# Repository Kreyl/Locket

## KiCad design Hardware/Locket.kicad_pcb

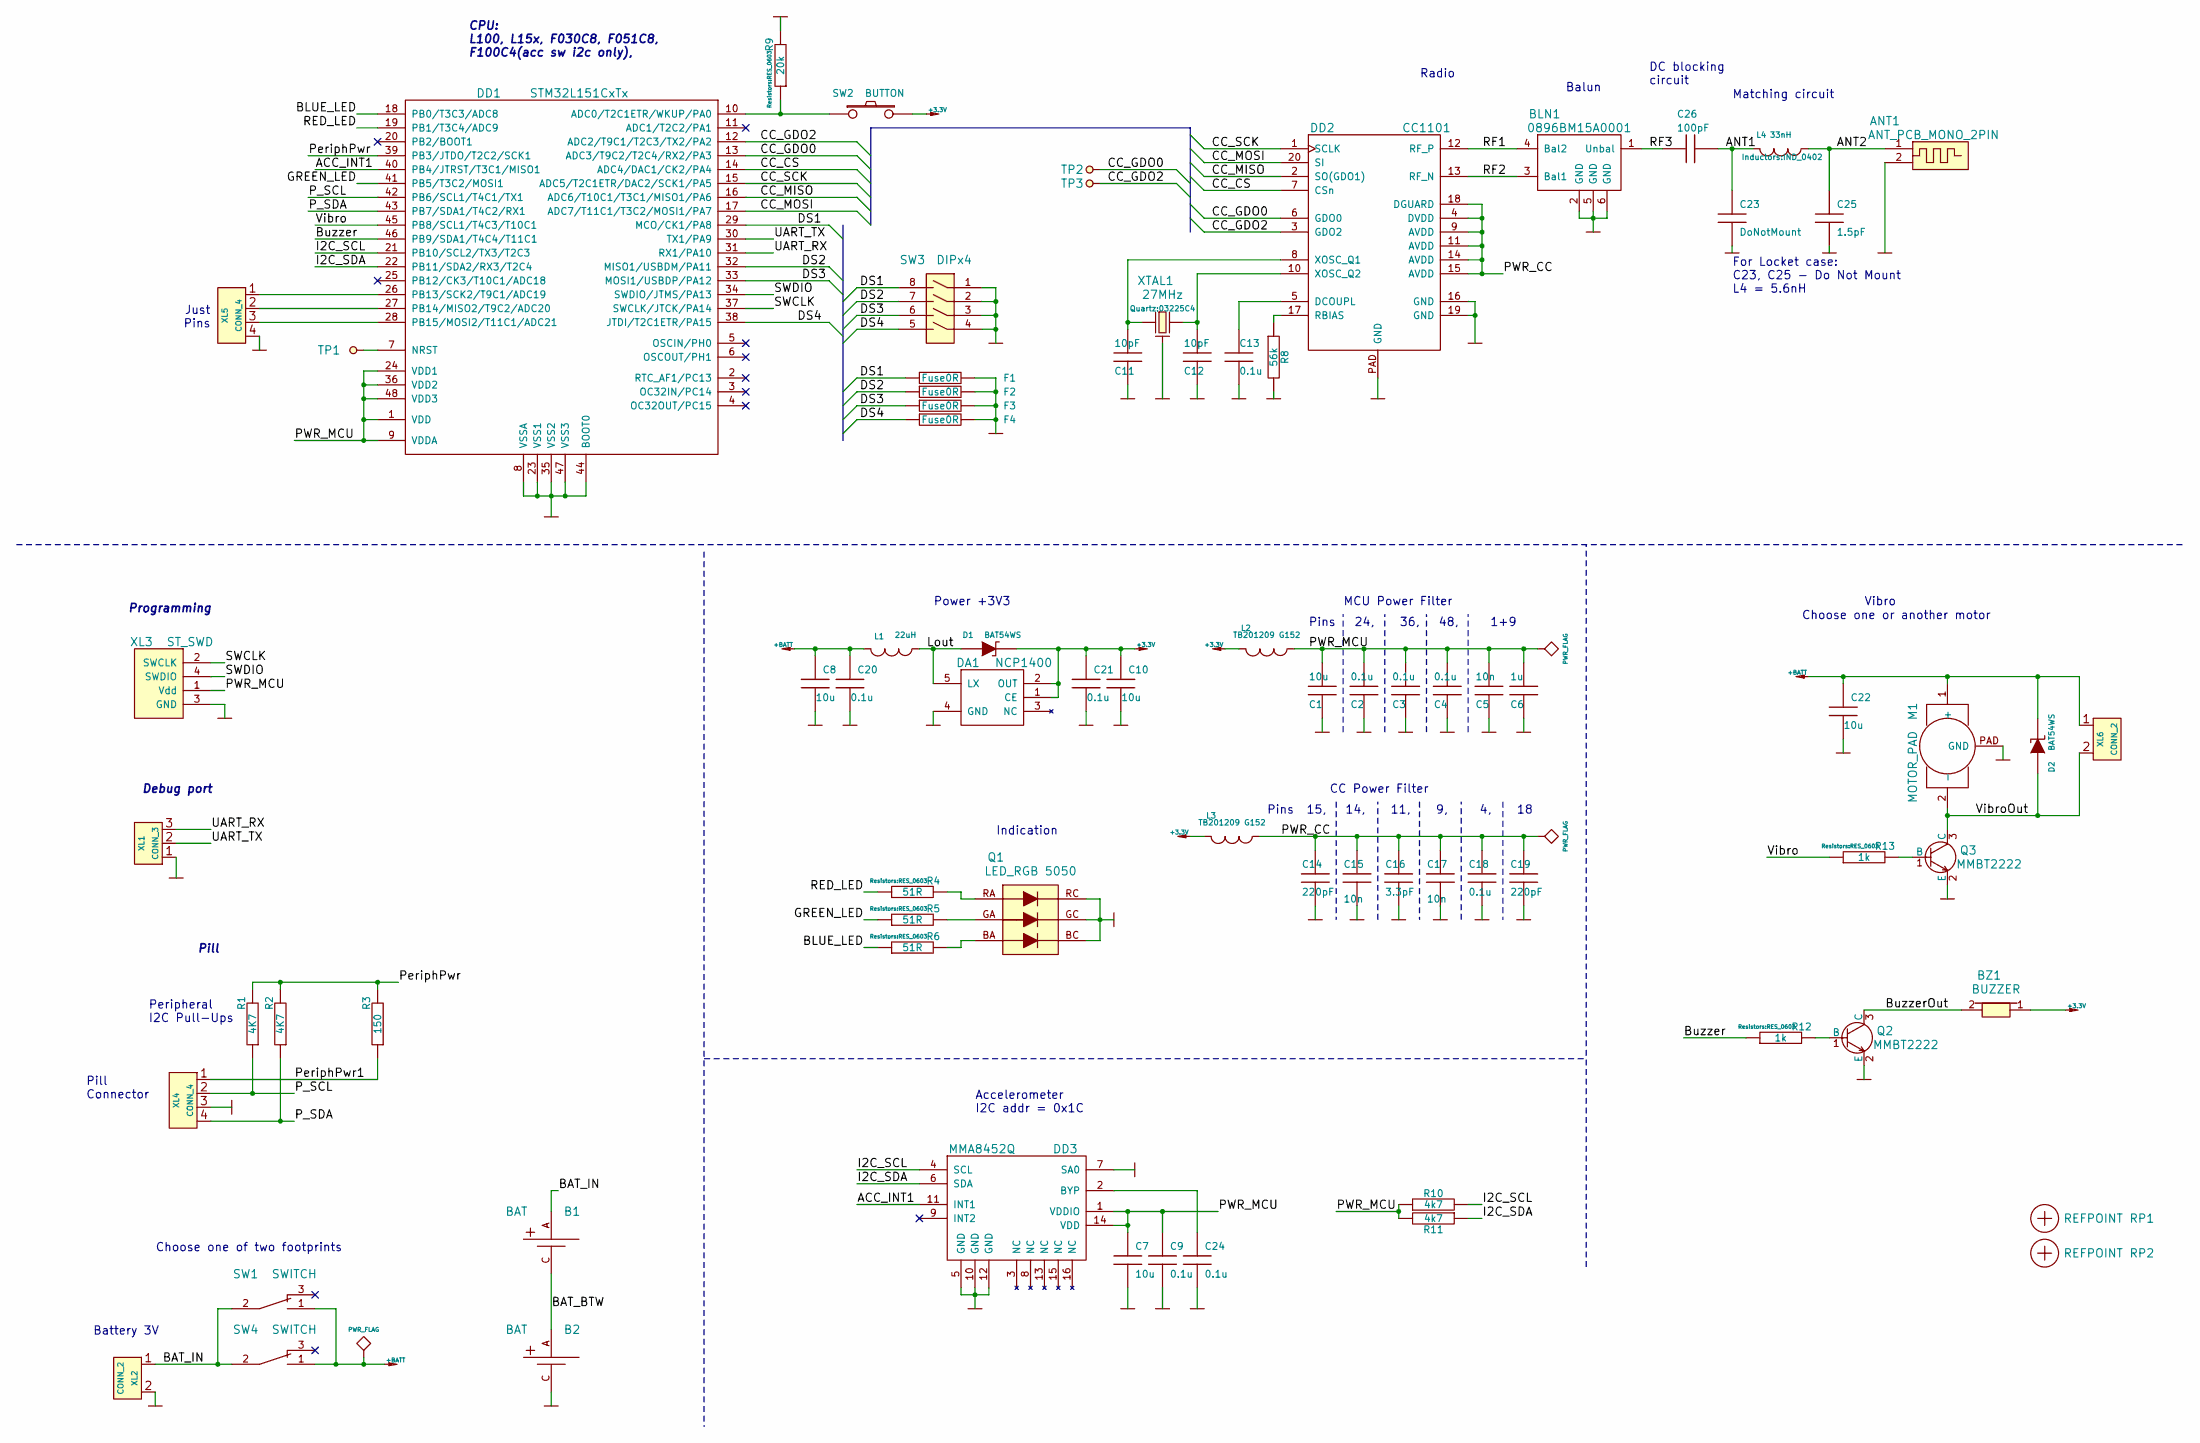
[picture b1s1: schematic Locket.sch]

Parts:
ANT1: ANT_PCB_MONO_2PIN; ANT_868_ROUND_F
B1, B2: BAT; BATTERY_AAA_X1
BLN1: 0896BM15A0001; BALUN_JOHANSON868
BZ1: BUZZER; BUZZER_HC0903
C1, C7, C8, C10, C22: 10u; CAP_0805
C2, C3, C4, C9, C13, C18, C20, C21, C24: 0.1u; CAP_0603
C5, C15, C17: 10n; CAP_0603
C6: 1u; CAP_0603
C11, C12: 10pF; CAP_0603
C14, C19: 220pF; CAP_0603
C16: 3.3pF; CAP_0603
C23: DoNotMount; CAP_0402
C25: 1.5pF; CAP_0402
C26: 100pF; CAP_0402
D1, D2: BAT54WS; SOD323
DA1: NCP1400; SOT23-5
DD1: STM32L151CxTx; LQFP48
DD2: CC1101; QFN20
DD3: MMA8452Q; QFN16_5_3
F1, F2, F3, F4: Fuse0R; RES_0603_FUSE
L1: 22uH; IND_1210_LQH32C
L2, L3: TB201209 G152; IND_0805
L4: 33nH; IND_0402
M1: MOTOR_PAD; MOTOR_KHN4NX
Q1: LED_RGB 5050; 5050
Q2, Q3: MMBT2222; SOT23-3
R1, R2: 4K7; RES_0603
R3: 150; RES_0603
R4, R5, R6: 51R; RES_0603
R8: 56k; RES_0603
R9: 20k; RES_0603
R10, R11: 4k7; RES_0603
R12, R13: 1k; RES_0603
RP1, RP2: REFPOINT; REF_POINT_1MM
SW1: SWITCH; SW_SS-6
SW2: BUTTON; BTN_6x6
SW3: DIPx4; DIP_SMD_X4
SW4: SWITCH; SW_SS-1P2T
TP1, TP2, TP3: TESTPOINT; TESTPOINT_1MM
XL1: CONN_3; PLS-3
XL2, XL6: CONN_2; PLS-2
XL3: ST_SWD; PLS-4
XL4, XL5: CONN_4; PLS-4
XTAL1: 27MHz; 03225C4

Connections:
+3.3V: BZ1.1, C10.1, C21.1, D1.C, DA1.1 (CE), DA1.2 (OUT), L2.2, L3.2, SW2.2
+BATT: C8.1, C20.1, C22.1, D2.C, L1.2, M1.1 (+), SW1.1, SW4.1, XL6.1
/ACC_INT1: DD1.40 (PB4/JTRST/T3C1/MISO1), DD3.11 (INT1)
/ANT1: C23.1, C26.1, L4.2
/ANT2: ANT1.1, C25.1, L4.1
/BAT_BTW: B1.C, B2.A
/BAT_IN: B1.A, SW1.2, SW4.2, XL2.1
/BLUE_LED: DD1.18 (PB0/T3C3/ADC8), R6.1
/Buzzer: DD1.46 (PB9/SDA1/T4C4/T11C1), R12.1
/BuzzerOut: BZ1.2, Q2.3 (C)
/CC_CS: DD1.14 (ADC4/DAC1/CK2/PA4), DD2.7 (CSn)
/CC_GDO0: DD1.13 (ADC3/T9C2/T2C4/RX2/PA3), DD2.6 (GDO0), TP2.1
/CC_GDO2: DD1.12 (ADC2/T9C1/T2C3/TX2/PA2), DD2.3 (GDO2), TP3.1
/CC_MISO: DD1.16 (ADC6/T10C1/T3C1/MISO1/PA6), DD2.2 (SO(GDO1))
/CC_MOSI: DD1.17 (ADC7/T11C1/T3C2/MOSI1/PA7), DD2.20 (SI)
/CC_SCK: DD1.15 (ADC5/T2C1ETR/DAC2/SCK1/PA5), DD2.1 (SCLK)
/DS1: DD1.29 (MCO/CK1/PA8), F1.1, SW3.8
/DS2: DD1.32 (MISO1/USBDM/PA11), F2.1, SW3.7
/DS3: DD1.33 (MOSI1/USBDP/PA12), F3.1, SW3.6
/DS4: DD1.38 (JTDI/T2C1ETR/PA15), F4.1, SW3.5
/GREEN_LED: DD1.41 (PB5/T3C2/MOSI1), R5.1
/I2C_SCL: DD1.21 (PB10/SCL2/TX3/T2C3), DD3.4 (SCL), R10.2
/I2C_SDA: DD1.22 (PB11/SDA2/RX3/T2C4), DD3.6 (SDA), R11.1
/Lout: D1.A, DA1.5 (LX), L1.1
/PWR_CC: C14.1, C15.1, C16.1, C17.1, C18.1, C19.1, DD2.4 (DVDD), DD2.9 (AVDD), DD2.11 (AVDD), DD2.14 (AVDD), DD2.15 (AVDD), DD2.18 (DGUARD), L3.1
/PWR_MCU: C1.1, C2.1, C3.1, C4.1, C5.1, C6.1, C7.1, C9.1, DD1.1 (VDD), DD1.9 (VDDA), DD1.24 (VDD1), DD1.36 (VDD2), DD1.48 (VDD3), DD3.1 (VDDIO), DD3.14 (VDD), L2.1, R10.1, R11.2, XL3.1 (Vdd)
/P_SCL: DD1.42 (PB6/SCL1/T4C1/TX1), R1.1, XL4.2 (PM)
/P_SDA: DD1.43 (PB7/SDA1/T4C2/RX1), R2.1, XL4.4
/PeriphPwr: DD1.39 (PB3/JTDO/T2C2/SCK1), R1.2, R2.2, R3.2
/PeriphPwr1: R3.1, XL4.1
/RED_LED: DD1.19 (PB1/T3C4/ADC9), R4.1
/RF1: BLN1.4 (Bal2), DD2.12 (RF_P)
/RF2: BLN1.3 (Bal1), DD2.13 (RF_N)
/RF3: BLN1.1 (Unbal), C26.2
/SWCLK: DD1.37 (SWCLK/JTCK/PA14), XL3.2 (SWCLK)
/SWDIO: DD1.34 (SWDIO/JTMS/PA13), XL3.4 (SWDIO)
/UART_RX: DD1.31 (RX1/PA10), XL1.3
/UART_TX: DD1.30 (TX1/PA9), XL1.2 (PM)
/Vibro: DD1.45 (PB8/SCL1/T4C3/T10C1), R13.1
/VibroOut: D2.A, M1.2 (-), Q3.3 (C), XL6.2 (PM)
GND: ANT1.2, B2.C, BLN1.2 (GND), BLN1.5 (GND), BLN1.6 (GND), C1.2, C2.2, C3.2, C4.2, C5.2, C6.2, C7.2, C8.2, C9.2, C10.2, C11.2, C12.2, C13.2, C14.2, C15.2, C16.2, C17.2, C18.2, C19.2, C20.2, C21.2, C22.2, C23.2, C24.2, C25.2, DA1.4 (GND), DD1.8 (VSSA), DD1.23 (VSS1), DD1.35 (VSS2), DD1.44 (BOOT0), DD1.47 (VSS3), DD2.16 (GND), DD2.19 (GND), DD2.PAD (GND), DD3.5 (GND), DD3.7 (SA0), DD3.10 (GND), DD3.12 (GND), F1.2, F2.2, F3.2, F4.2, M1.PAD (GND), Q1.BC (B), Q1.GC (G), Q1.RC, Q2.2 (E), Q3.2 (E), R8.2, R9.2, SW3.1, SW3.2, SW3.3, SW3.4, XL1.1, XL2.2 (PM), XL3.3 (GND), XL4.3, XL5.4, XTAL1.H
unnamed: C11.1, DD2.8 (XOSC_Q1), XTAL1.1
unnamed: C12.1, DD2.10 (XOSC_Q2), XTAL1.2
unnamed: C13.1, DD2.5 (DCOUPL)
unnamed: C24.1, DD3.2 (BYP)
unnamed: DD1.7 (NRST), TP1.1
unnamed: DD1.10 (ADC0/T2C1ETR/WKUP/PA0), R9.1, SW2.1
unnamed: DD1.26 (PB13/SCK2/T9C1/ADC19), XL5.1
unnamed: DD1.27 (PB14/MISO2/T9C2/ADC20), XL5.2 (PM)
unnamed: DD1.28 (PB15/MOSI2/T11C1/ADC21), XL5.3
unnamed: DD2.17 (RBIAS), R8.1
unnamed: Q1.BA, R6.2
unnamed: Q1.GA, R5.2
unnamed: Q1.RA, R4.2
unnamed: Q2.1 (B), R12.2
unnamed: Q3.1 (B), R13.2

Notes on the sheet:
Battery 3V
Radio
Matching circuit
Debug port
Programming
CPU: L100, L15x, F030C8, F051C8, F100C4(acc sw i2c only),
Indication
Peripheral I2C Pull-Ups
Pill Connector
Pill
Just Pins
Power +3V3
Vibro
Accelerometer I2C addr = 0x1C
Choose one of two footprints
Choose one or another motor
Balun
DC blocking circuit
For Locket case: C23, C25 - Do Not Mount L4 = 5.6nH
MCU Power Filter
Pins 24, 36, 48, 1+9
CC Power Filter
Pins 15, 14, 11, 9, 4, 18

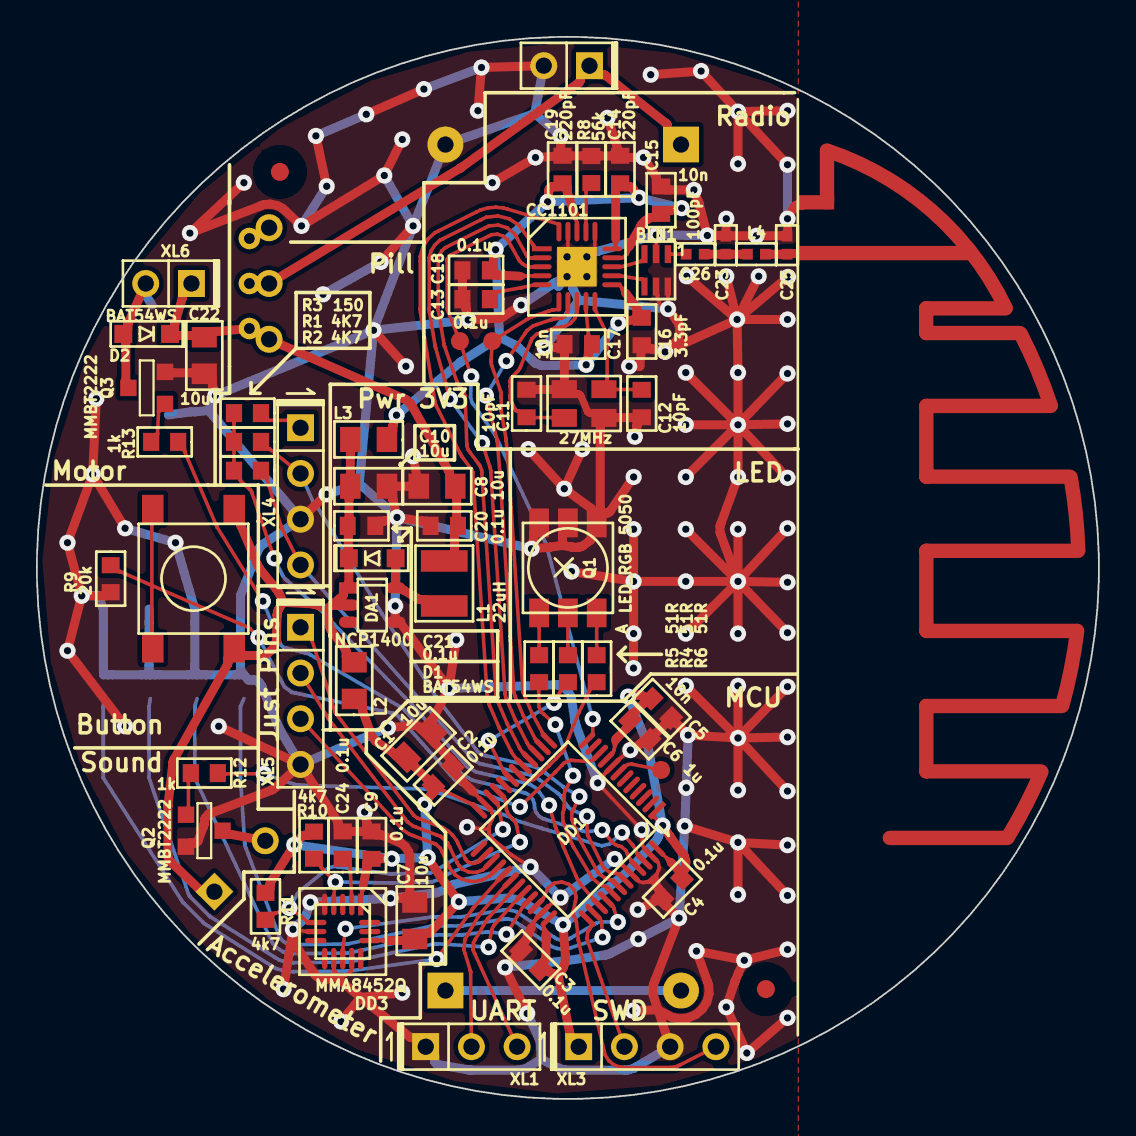
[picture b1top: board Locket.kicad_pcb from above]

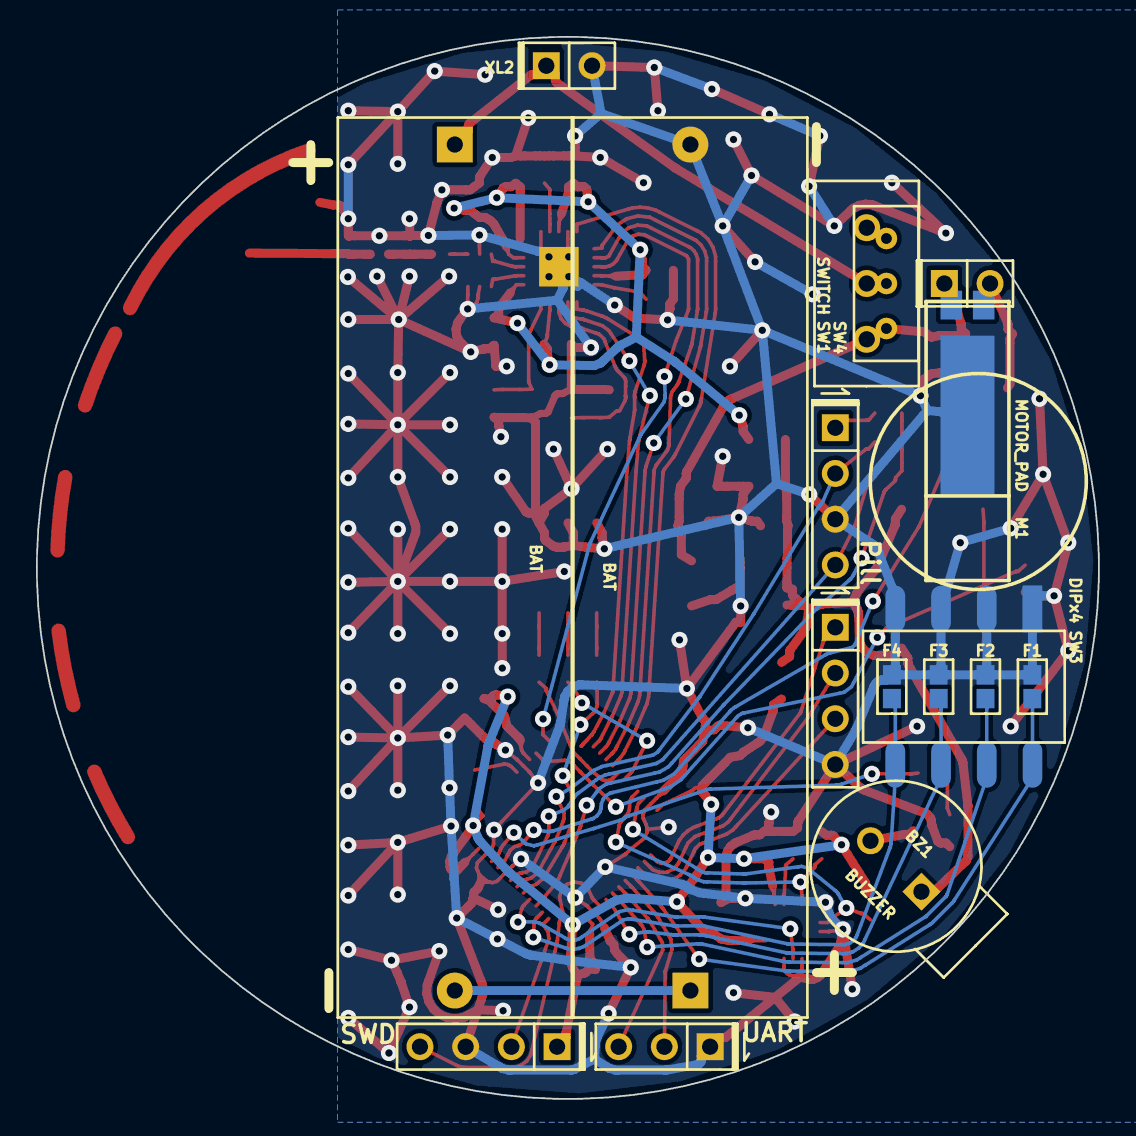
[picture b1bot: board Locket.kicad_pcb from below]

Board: 2 copper layers, 59.0 x 59.0 mm, 77 parts (12 on the bottom side), 56 nets.

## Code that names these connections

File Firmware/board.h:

/*
 * board.h
 *
 *  Created on: 12 ñåíò. 2015 ã.
 *      Author: Kreyl
 */

#pragma once

#include <inttypes.h>

// ==== General ====
#define BOARD_NAME          "LocketOld"
#define APP_NAME            "KessDetector"

// ==== High-level peripery control ====
#define PILL_ENABLED        FALSE
#define BEEPER_ENABLED      FALSE
#define BTN_ENABLED         FALSE

// MCU type as defined in the ST header.
#define STM32L151xB

// Freq of external crystal if any. Leave it here even if not used.
#define CRYSTAL_FREQ_HZ     12000000

#define SYS_TIM_CLK         (Clk.APB1FreqHz)
#define I2C1_ENABLED        FALSE
#define I2C_USE_SEMAPHORE   TRUE
#define ADC_REQUIRED        TRUE

#if 1 // ========================== GPIO =======================================
// PortMinTim_t: GPIO, Pin, Tim, TimChnl, invInverted, omPushPull, TopValue
// UART
#define UART_GPIO       GPIOA
#define UART_TX_PIN     9
#define UART_RX_PIN     10
#define UART_AF         AF7 // for USART1 @ GPIOA

// LED
#define LED_R_PIN       { GPIOB, 1, TIM3, 4, invNotInverted, omPushPull, 255 }
#define LED_G_PIN       { GPIOB, 0, TIM3, 3, invNotInverted, omPushPull, 255 }
#define LED_B_PIN       { GPIOB, 5, TIM3, 2, invNotInverted, omPushPull, 255 }

// Button
#define BTN_PIN         { GPIOA, 0, pudPullDown }

// Vibro
#define VIBRO_TOP       99
#define VIBRO_PIN       { GPIOB, 8, TIM4, 3, invNotInverted, omPushPull, VIBRO_TOP }

// Beeper
#define BEEPER_TOP      22
#define BEEPER_PIN      { GPIOB, 15, TIM11, 1, invNotInverted, omPushPull, BEEPER_TOP }

// DIP switch
#define DIP_SW_CNT      4
#define DIP_SW1         { GPIOA, 8,  pudPullUp }
#define DIP_SW2         { GPIOA, 11, pudPullUp }
#define DIP_SW3         { GPIOA, 12, pudPullUp }
#define DIP_SW4         { GPIOA, 15, pudPullUp }

// I2C
#if I2C1_ENABLED
#define I2C1_GPIO       GPIOB
#define I2C1_SCL        6
#define I2C1_SDA        7
#define I2C1_AF         AF4
#endif

// Pill power
#define PILL_PWR_PIN    { GPIOB, 3, omPushPull }

// Radio
#define CC_GPIO         GPIOA
#define CC_GDO2         2
#define CC_GDO0         3
#define CC_SCK          5
#define CC_MISO         6
#define CC_MOSI         7
#define CC_CS           4
// Input pin (do not touch)
#define CC_GDO0_IRQ     { CC_GPIO, CC_GDO0, pudNone }

#endif // GPIO

#if 1 // ========================= Timer =======================================
#endif // Timer

#if I2C1_ENABLED // ====================== I2C ================================
#define I2C1_BAUDRATE   400000
#endif

#if 1 // =========================== SPI =======================================
#define CC_SPI          SPI1
#define CC_SPI_AF       AF5
#endif

#if 1 // ========================== USART ======================================
#define UART            USART1
#define UART_TX_REG     UART->DR
#define UART_RX_REG     UART->DR
#endif

#if ADC_REQUIRED // ======================= Inner ADC ==========================
// Clock divider: clock is generated from the APB2
#define ADC_CLK_DIVIDER		adcDiv2

// ADC channels
//#define BAT_CHNL 	        1

#define ADC_VREFINT_CHNL    17  // All 4xx, F072 and L151 devices. Do not change.
#define ADC_CHANNELS        { ADC_VREFINT_CHNL }
#define ADC_CHANNEL_CNT     1   // Do not use countof(AdcChannels) as preprocessor does not know what is countof => cannot check
#define ADC_SAMPLE_TIME     ast96Cycles
#define ADC_SAMPLE_CNT      8   // How many times to measure every channel

#define ADC_SEQ_LEN         (ADC_SAMPLE_CNT * ADC_CHANNEL_CNT)

#endif

#if 1 // =========================== DMA =======================================
#define STM32_DMA_REQUIRED  TRUE
// ==== Uart ====
#define UART_DMA_TX     STM32_DMA1_STREAM4
#define UART_DMA_RX     STM32_DMA1_STREAM5
#define UART_DMA_CHNL   0   // Dummy

#if I2C1_ENABLED // ==== I2C ====
#define I2C1_DMA_TX     STM32_DMA1_STREAM6
#define I2C1_DMA_RX     STM32_DMA1_STREAM7
#endif

#if ADC_REQUIRED
#define ADC_DMA         STM32_DMA1_STREAM1
#define ADC_DMA_MODE    STM32_DMA_CR_CHSEL(0) |   /* dummy */ \
                        DMA_PRIORITY_LOW | \
                        STM32_DMA_CR_MSIZE_HWORD | \
                        STM32_DMA_CR_PSIZE_HWORD | \
                        STM32_DMA_CR_MINC |       /* Memory pointer increase */ \
                        STM32_DMA_CR_DIR_P2M |    /* Direction is peripheral to memory */ \
                        STM32_DMA_CR_TCIE         /* Enable Transmission Complete IRQ */
#endif // ADC

#endif // DMA

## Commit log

2015-04-10 + SCH nearing completion + PCB in progress + RF Simulation in progress
2015-04-10 + Accelerometer + Proceeding with antenna & PCB
2015-04-10 + Additional footprints for motor and switch
2015-04-12 + PCB routed, but DRC not tested
2015-04-13 * PCB sent to production
2015-04-24 First firmware attempt: +LED + Uart Other not tested
2015-04-26 + Antenna matched, log doc added
2015-04-28 Proceeding with vibro
2015-05-04 Salem Transmitter started
2015-05-04 + Led pwr src disabled Release candidate
2015-05-16 + Locket hardware v2 * switch to 10 kBit
2015-05-17 Smth strange with UART
2015-05-17 + Terminal macro * Uart Cmd RX changed to EVT_NEW_UART_CMD
2015-05-17 + Get / Set ID
2015-05-17 + Transmitter (not tested) + Receiver in progress
2015-05-27 + ignore wrl
2015-05-28 Digging a hole. In deep progress. Nothing works.
2015-05-29 Adapting chibios 2.6.8 for f030
2015-05-29 All was lost at moment when TIM3 is found to be the only option for time counting. Alas.
2015-05-30 App starts, LED & UART work. CC Init Error.
2015-06-07 Last changes for F030
2015-06-07 * Switch to L MCU + LED ok + CC Init ok
2015-06-07 + Antenna matched, sch updated + Vibro works
2015-06-07 + Radio works
2015-06-08 "Each feels each" not implemented, other done
2015-06-09 * kl_lib renewed * "Each feels other" mode in progress
2015-06-10 + TxRx + Version is now DateTime Something wrong with timings at TxRx
2015-06-12 * Radio switched to 250 kBit/s + CountingBuffer * one buffer instead of two in radio-to-main logic
2015-06-13 + Indication of mode - Startup indication
2015-06-13 * Rx and Tx timings lowered to decrease power consumption. + Consumption.xlsx
2015-06-13 + GetColor / SetColor UART commands + ColorSetup mode + EEPROM color load/save
2015-06-13 * Colors sequence changed + Case STLs added
2015-06-15 Release Candidate * Color order in ColorSetup mode * Radio Power Levels modified + Transmitter mode indication + Flash utility
2015-06-17 Release * Fixed: did not indicate RxVibro when switched on
2015-06-23 + sleep modes (not checked)
2015-06-23 Release Candidate
2015-06-26 + TxPower set by DIP * On sequence made immediate * Dip Check every second
2015-06-27 Release * Switch on/off at once
2015-07-04 * Klaus implemented on hardware v1
2015-08-16 * kl_lib: universal virtual timer + TX on/off
2015-08-16 All seems working. Indication and timings are subject to change.
2015-08-16 Release * Btn: pull-down enabled * TX pwr = 10dBm
2015-10-29 Release
2015-12-11 Minor removals
2015-12-11 To check
2015-12-11 + Dip controlled sensitivity + Minor indication changes Release
2016-01-12 Proceeding
2016-01-12 + 9D mems
2016-03-02 Debugging
2016-03-02 Seems working
2016-03-02 + rssi threshold
2016-07-23 + color iteration by button
2016-07-23 + color is set and transmitted
2016-07-23 + ColorTable
2016-07-23 Beginning
2016-07-25 Rchnls moved to 0...8
2016-07-26 * Color switched to blue Release
2016-07-28 + Black color to allow switching off
2016-09-06 Tx/Rx works ok
2016-09-06 Some cleanup RC
